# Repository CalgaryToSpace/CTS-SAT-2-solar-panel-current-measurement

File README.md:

# CTS-SAT-2-solar-panel-current-measurement

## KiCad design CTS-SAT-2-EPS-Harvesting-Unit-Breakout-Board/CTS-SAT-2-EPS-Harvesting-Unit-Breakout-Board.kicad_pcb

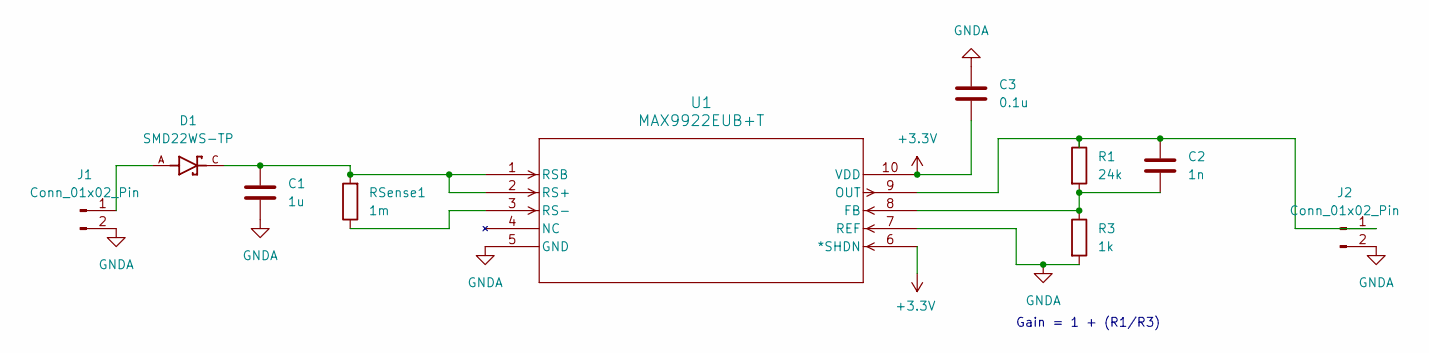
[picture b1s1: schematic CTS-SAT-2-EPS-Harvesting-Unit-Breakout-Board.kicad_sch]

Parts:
C1: 1u; C_1206_3216Metric
C2: 1n; C_1206_3216Metric
C3: 0.1u; C_1206_3216Metric
D1: SMD22WS-TP; SOD2512X115N; PARTREV 3-4-12012020
J1, J2: Conn_01x02_Pin; PinHeader_1x02_P2.54mm_Vertical
R1: 24k; R_1206_3216Metric
R3: 1k; R_1206_3216Metric
RSense1: 1m; R_1206_3216Metric
U1: MAX9922EUB+T; 21-0061L_MXM

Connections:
+3.3V: C3.2, U1.6 (*SHDN), U1.10 (VDD)
GNDA: C1.2, C3.1, J1.2, J2.2, R3.2, U1.5 (GND), U1.7 (REF)
unnamed: D1.A, J1.1
unnamed: C2.1, J2.1, R1.1, U1.9 (OUT)
unnamed: C2.2, R1.2, R3.1, U1.8 (FB)
unnamed: C1.1, D1.C, RSense1.2, U1.1 (RSB), U1.2 (RS+)
unnamed: RSense1.1, U1.3 (RS-)

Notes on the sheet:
Gain = 1 + (R1/R3)

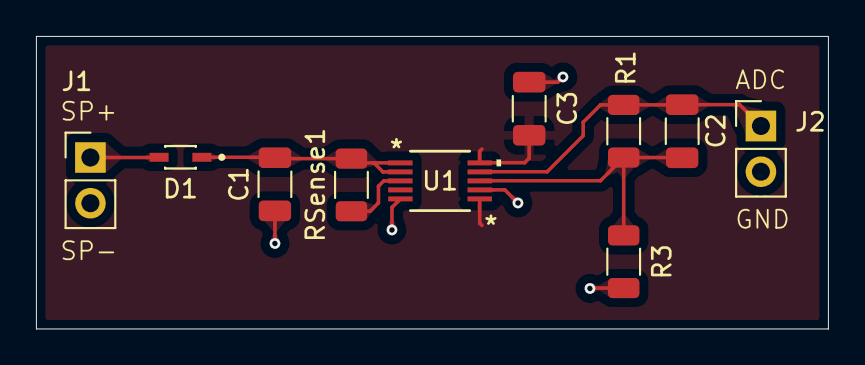
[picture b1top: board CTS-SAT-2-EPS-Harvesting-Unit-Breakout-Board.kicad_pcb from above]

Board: 2 copper layers, 44.0 x 16.2 mm, 10 parts (0 on the bottom side), 7 nets.

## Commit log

2026-04-18 PCB files
2026-04-18 firmware
2026-04-25 first rev
